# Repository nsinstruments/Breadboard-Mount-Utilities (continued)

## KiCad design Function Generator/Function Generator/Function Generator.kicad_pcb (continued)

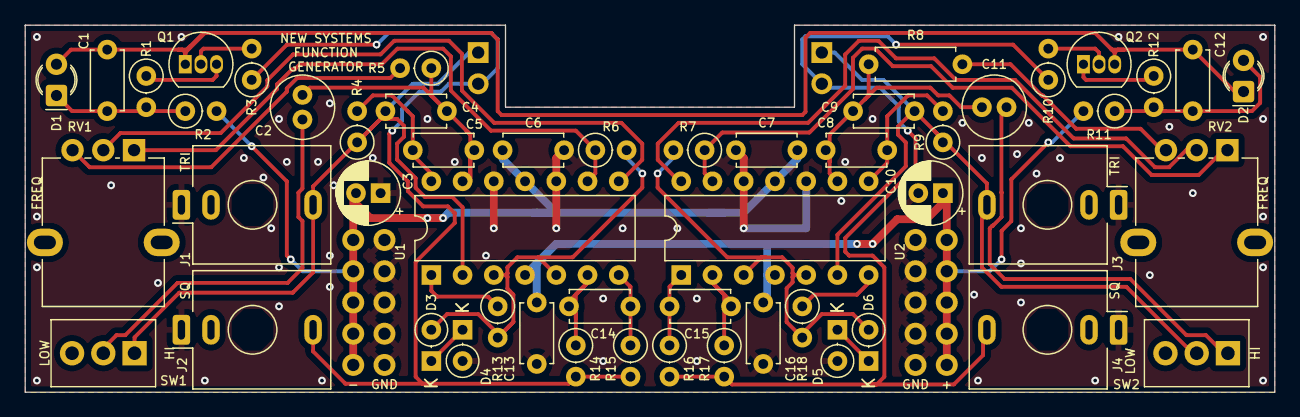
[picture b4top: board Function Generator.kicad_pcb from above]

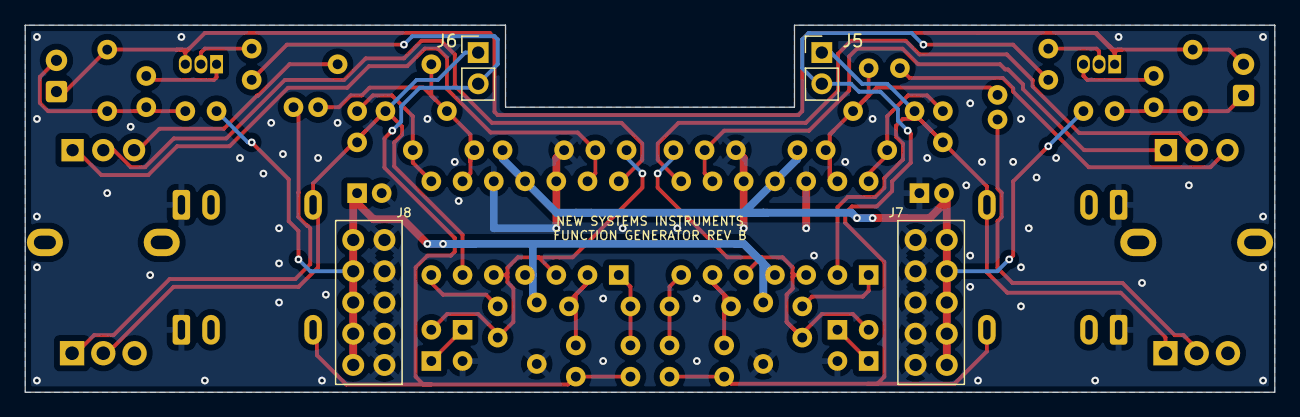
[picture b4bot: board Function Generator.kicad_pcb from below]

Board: 2 copper layers, 101.6 x 29.8 mm, 56 parts (4 on the bottom side), 36 nets.

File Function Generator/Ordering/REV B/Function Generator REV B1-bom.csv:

Reference,Value,Distributor,Manufacturer,Part No.,Quantity,Price
C1 C6 C7 C12 C13 C16,100n,"Mouser,Digi-Key",Vishay,K104K15X7RF5TH5,6,$0.24 
C2 C11,1u,"Mouser,Digi-Key",Nichicon,UES1H010MDM,2,$0.49 
C3 C10,10u,"Mouser,Digi-Key",Nichicon,UPS1V100MDD,2,$0.33 
C4 C9,1.5n C0G,"Mouser,Digi-Key",TDK,FG28C0G1H152J,2,$0.31 
C5 C8 C14 C15,100p,"Mouser,Digi-Key",Vishay,K101J15C0GF5TH5,4,$0.27 
D1 D2,WP710A10ED,"Mouser,Digi-Key",Kingbright,WP710A10ID,2,$0.35 
D3 D4 D5 D6,BZX79C5V1,"Mouser,Digi-Key",ON Semiconductor,BZX79C5V1,4,$0.16 
J5 J6,1x2 pin 2.54mm,"Mouser,Digi-Key",Harwin,M20-9770242,2,$0.17 
J7 J8,2x5 pin 2.54mm,"Mouser,Digi-Key",Harwin,M20-9760542,2,$0.45 
Q1 Q2,2N3906,"Mouser,Digi-Key",Central Semiconductor,2N3906,2,$0.44 
R1 R12,680,"Mouser,Digi-Key",Yageo,MFR-25FRF52-680R,2,$0.12 
R2 R11,5.6k,"Mouser,Digi-Key",Yageo,MFR-25FRF52-5K6,2,$0.12 
R3 R6 R7 R10 R14 R17,47k,"Mouser,Digi-Key",Yageo,MFR-25FRF52-47K,6,$0.08 
R4 R9 R15 R16,1k,"Mouser,Digi-Key",Yageo,MFR-25FRF52-1K,4,$0.12 
R5 R8,12k,"Mouser,Digi-Key",Yageo,MFR-25FRF52-12K,2,$0.10 
R13 R18,18k,"Mouser,Digi-Key",Yageo,MFR-25FRF52-18K,2,$0.12 
U1 U2,TL074,"Mouser,Digi-Key",Texas Instruments,TL074CN,2,$0.86 
,,,,,,
J1 J2 J3 J4,3.5mm Jack,"Thonk, Antique Electronic Supply, Synthcube, Modular Addict",Qing Pu,WQP518MA/PJ301,4,$0.49 
RV1 RV2,100kA,"Thonk, Antique Electronic Supply, Love My Switches, Smallbear, Synthcube, Modular Addict, Tayda",Alpha/Various,9mm Vertical 100k Audio/Log Taper,2,$1.92 
SW1 SW2,SPDT,"Thonk, Love My Switches, Smallbear, Synthcube, LCSC",Taiway/Various,Sub-Miniature SPDT ON-ON Toggle,2,$1.95

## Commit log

2022-04-29 Preparing for open source release
2022-04-29 updated documentation and license
2022-04-29 renaming read mes to make github happy
2022-08-20 modified BOM to help with part availability
2026-05-14 updated breadboard power to REV 3
2026-05-14 Updated Voltage Source to REV 5
2026-05-22 changed current limiting resistors and 0V resistors, and cleaned up silk layer
2026-05-22 adjusted readme to account for higher 0V resistance value
